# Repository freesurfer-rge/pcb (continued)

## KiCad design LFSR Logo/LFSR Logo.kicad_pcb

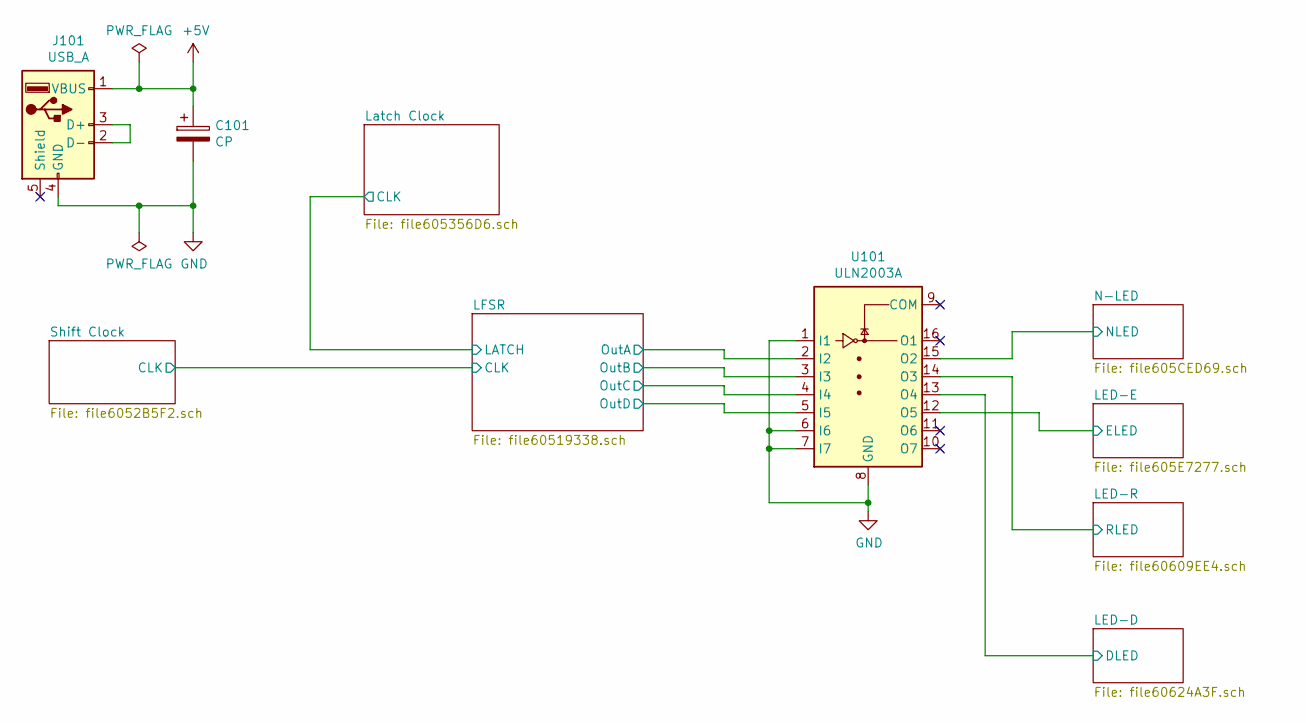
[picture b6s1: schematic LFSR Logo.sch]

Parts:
C101: CP; CP_Radial_D4.0mm_P1.50mm
J101: USB_A; USB_A_CONNFLY_DS1095-WNR0
U101: ULN2003A; DIP-16_W7.62mm

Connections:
+5V: C101.1, J101.1 (VBUS); also elsewhere on the board
/LED-D/DLED: U101.13 (O4); also elsewhere on the board
/LED-E/ELED: U101.12 (O5); also elsewhere on the board
/LED-R/RLED: U101.14 (O3); also elsewhere on the board
/LFSR/OutA: U101.2 (I2); also elsewhere on the board
/LFSR/OutB: U101.3 (I3); also elsewhere on the board
/LFSR/OutC: U101.4 (I4); also elsewhere on the board
/LFSR/OutD: U101.5 (I5); also elsewhere on the board
/N-LED/NLED: U101.15 (O2); also elsewhere on the board
GND: C101.2, J101.4 (GND), U101.1 (I1), U101.6 (I6), U101.7 (I7), U101.8 (GND); also elsewhere on the board
unnamed: J101.2 (D-), J101.3 (D+)

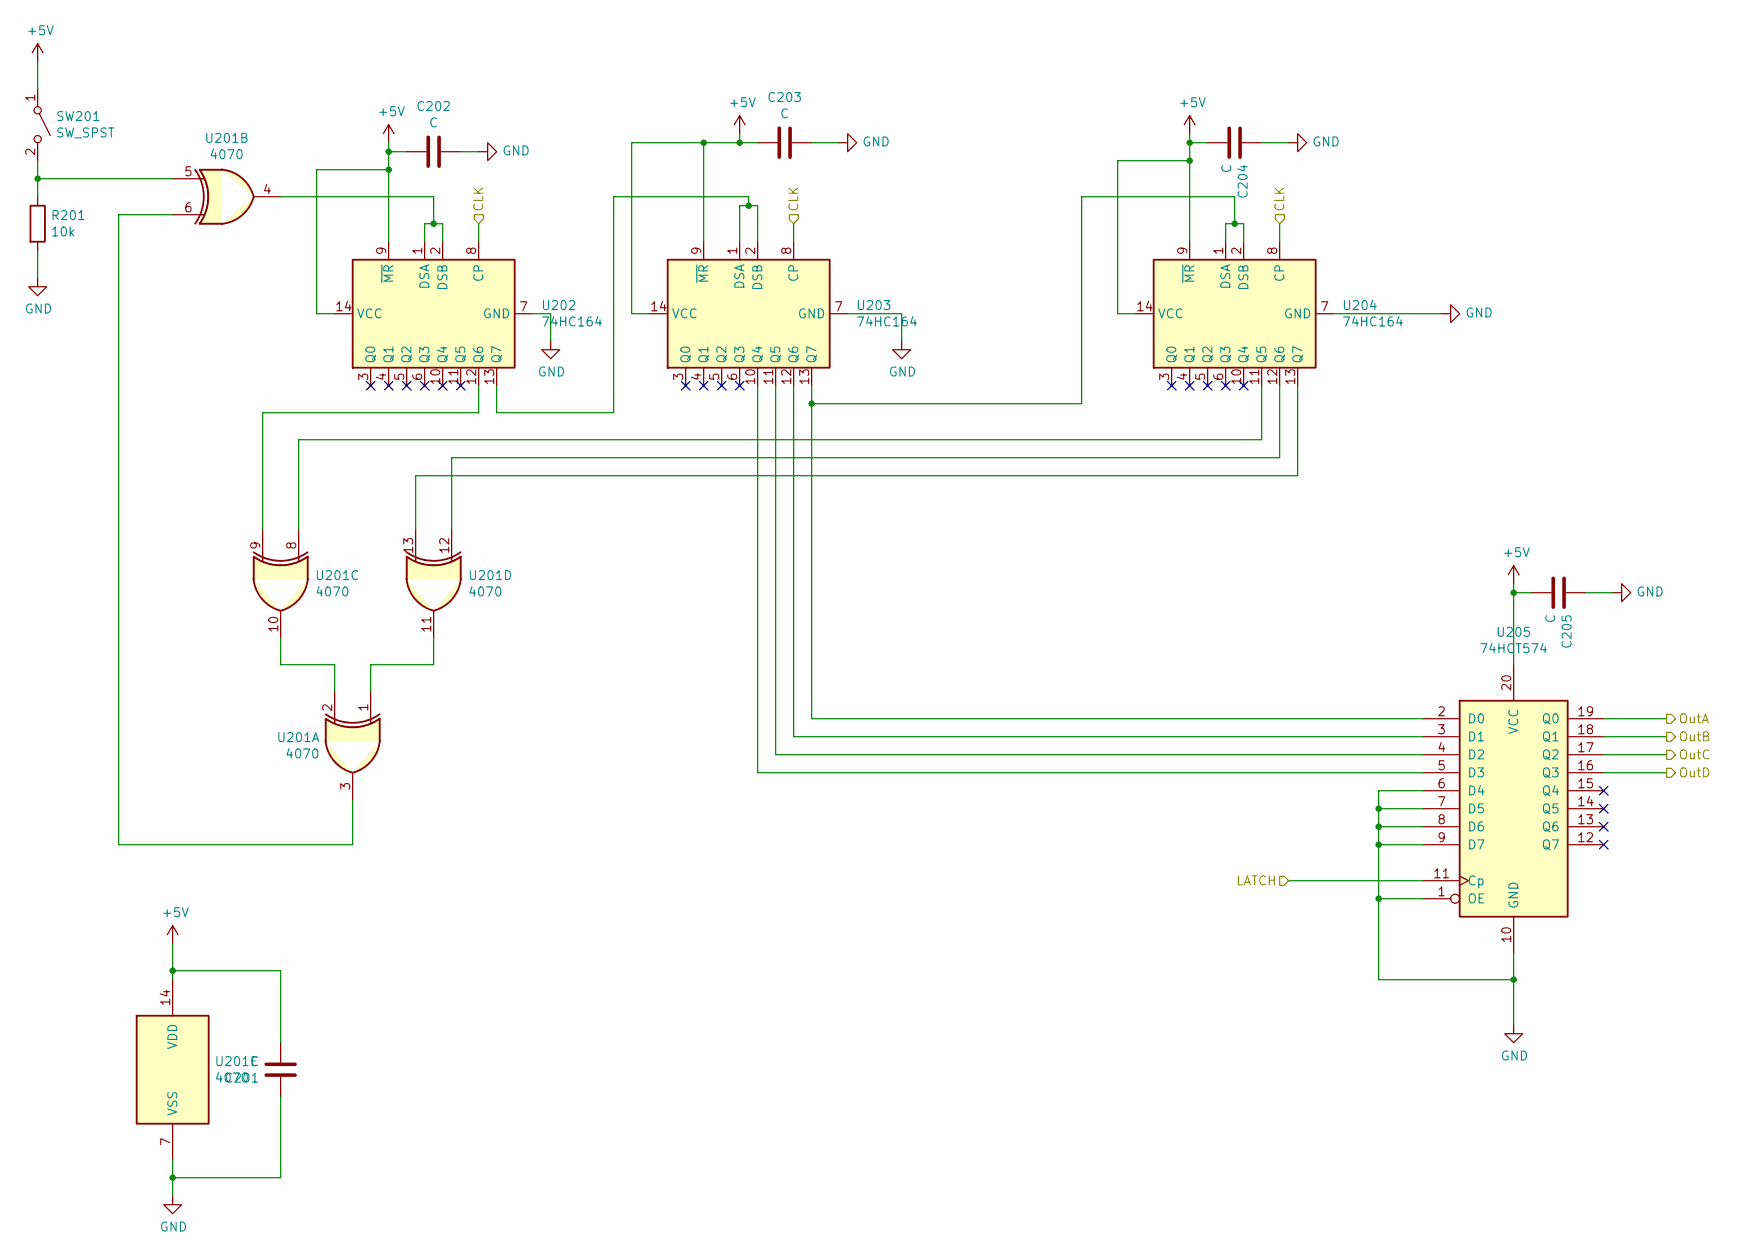
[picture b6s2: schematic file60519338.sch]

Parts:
C201, C202, C203, C204, C205: C; C_Disc_D4.3mm_W1.9mm_P5.00mm
R201: 10k; R_Axial_DIN0207_L6.3mm_D2.5mm_P7.62mm_Horizontal
SW201: SW_SPST; SW_PUSH_6mm
U201: 4070
U202, U203, U204: 74HC164; DIP-14_W7.62mm
U205: 74HCT574; DIP-20_W7.62mm

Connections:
+5V: C201.2, C202.2, C203.2, C204.2, C205.2, SW201.1 (A), U201.14 (VDD), U202.9 (~MR), U202.14 (VCC), U203.9 (~MR), U203.14 (VCC), U204.9 (~MR), U204.14 (VCC), U205.20 (VCC); also elsewhere on the board
/LFSR/CLK: U202.8 (CP), U203.8 (CP), U204.8 (CP); also elsewhere on the board
/LFSR/OutA: U205.19 (Q0); also elsewhere on the board
/LFSR/OutB: U205.18 (Q1); also elsewhere on the board
/LFSR/OutC: U205.17 (Q2); also elsewhere on the board
/LFSR/OutD: U205.16 (Q3); also elsewhere on the board
/Latch Clock/CLK: U205.11 (Cp); also elsewhere on the board
GND: C201.1, C202.1, C203.1, C204.1, C205.1, R201.2, U201.7 (VSS), U202.7 (GND), U203.7 (GND), U204.7 (GND), U205.1 (OE), U205.6 (D4), U205.7 (D5), U205.8 (D6), U205.9 (D7), U205.10 (GND); also elsewhere on the board
unnamed: R201.1, SW201.2 (B), U201.5
unnamed: U201.1, U201.11
unnamed: U201.3, U201.6
unnamed: U201.4, U202.1 (DSA), U202.2 (DSB)
unnamed: U201.8, U204.11 (Q5)
unnamed: U201.9, U202.12 (Q6)
unnamed: U201.2, U201.10
unnamed: U201.12, U204.12 (Q6)
unnamed: U201.13, U204.13 (Q7)
unnamed: U202.13 (Q7), U203.1 (DSA), U203.2 (DSB)
unnamed: U203.10 (Q4), U205.5 (D3)
unnamed: U203.11 (Q5), U205.4 (D2)
unnamed: U203.12 (Q6), U205.3 (D1)
unnamed: U203.13 (Q7), U204.1 (DSA), U204.2 (DSB), U205.2 (D0)

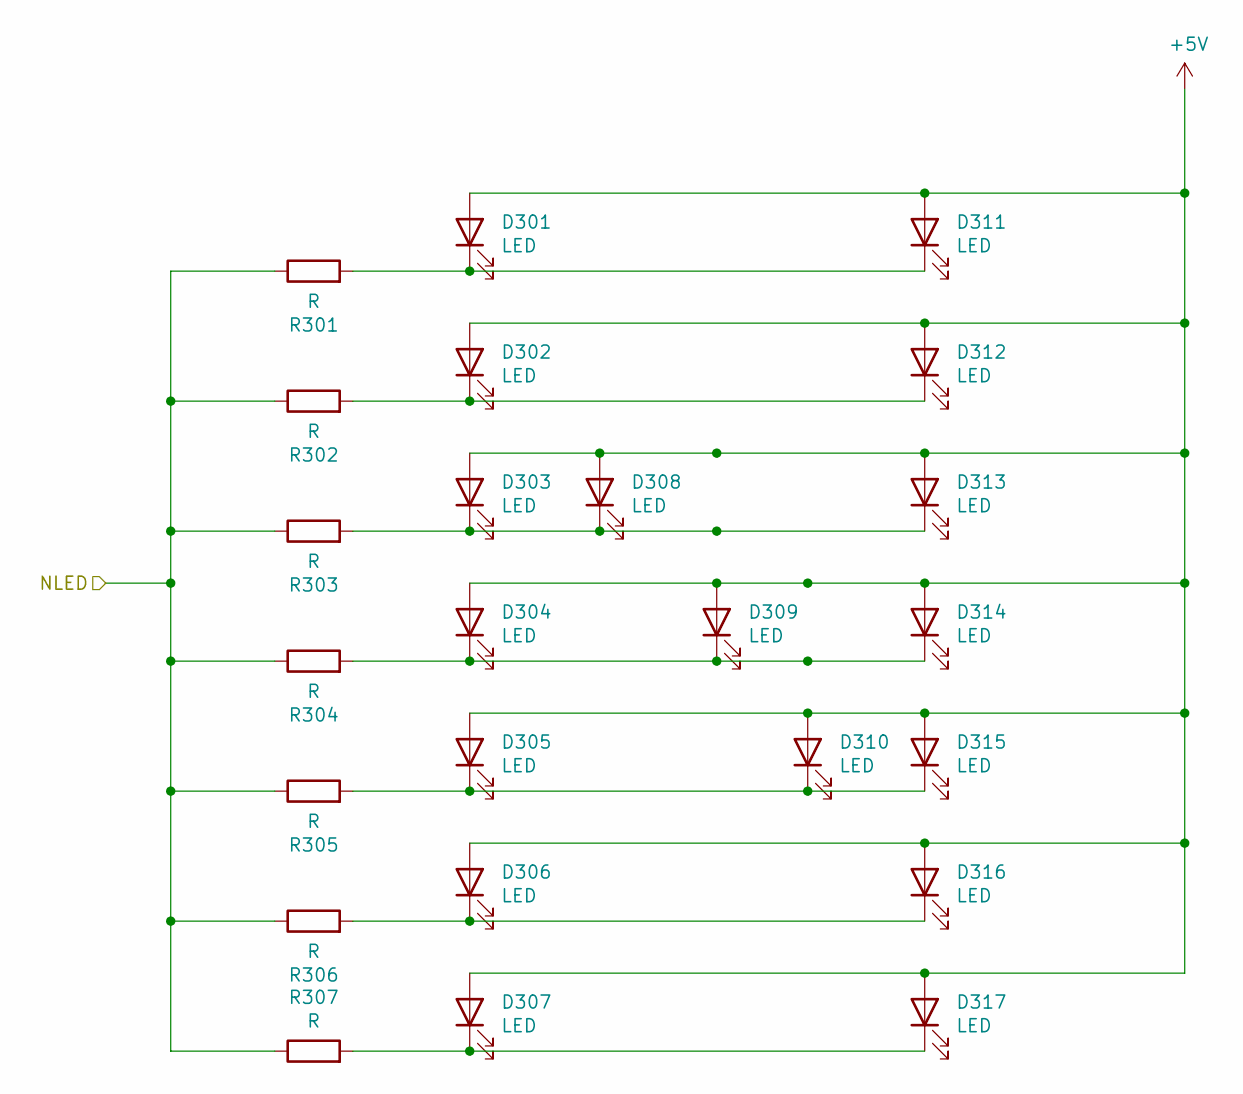
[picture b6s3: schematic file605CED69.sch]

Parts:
D301, D302, D303, D304, D305, D306, D307, D308, D309, D310, D311, D312, D313, D314, D315, D316, D317: LED; LED_D5.0mm
R301, R302, R303, R304, R305, R306, R307: R; R_Axial_DIN0207_L6.3mm_D2.5mm_P7.62mm_Horizontal

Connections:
+5V: D301.2 (A), D302.2 (A), D303.2 (A), D304.2 (A), D305.2 (A), D306.2 (A), D307.2 (A), D308.2 (A), D309.2 (A), D310.2 (A), D311.2 (A), D312.2 (A), D313.2 (A), D314.2 (A), D315.2 (A), D316.2 (A), D317.2 (A); also elsewhere on the board
/N-LED/NLED: R301.1, R302.1, R303.1, R304.1, R305.1, R306.1, R307.1; also elsewhere on the board
unnamed: D301.1 (K), D311.1 (K), R301.2
unnamed: D302.1 (K), D312.1 (K), R302.2
unnamed: D303.1 (K), D308.1 (K), D313.1 (K), R303.2
unnamed: D304.1 (K), D309.1 (K), D314.1 (K), R304.2
unnamed: D305.1 (K), D310.1 (K), D315.1 (K), R305.2
unnamed: D306.1 (K), D316.1 (K), R306.2
unnamed: D307.1 (K), D317.1 (K), R307.2

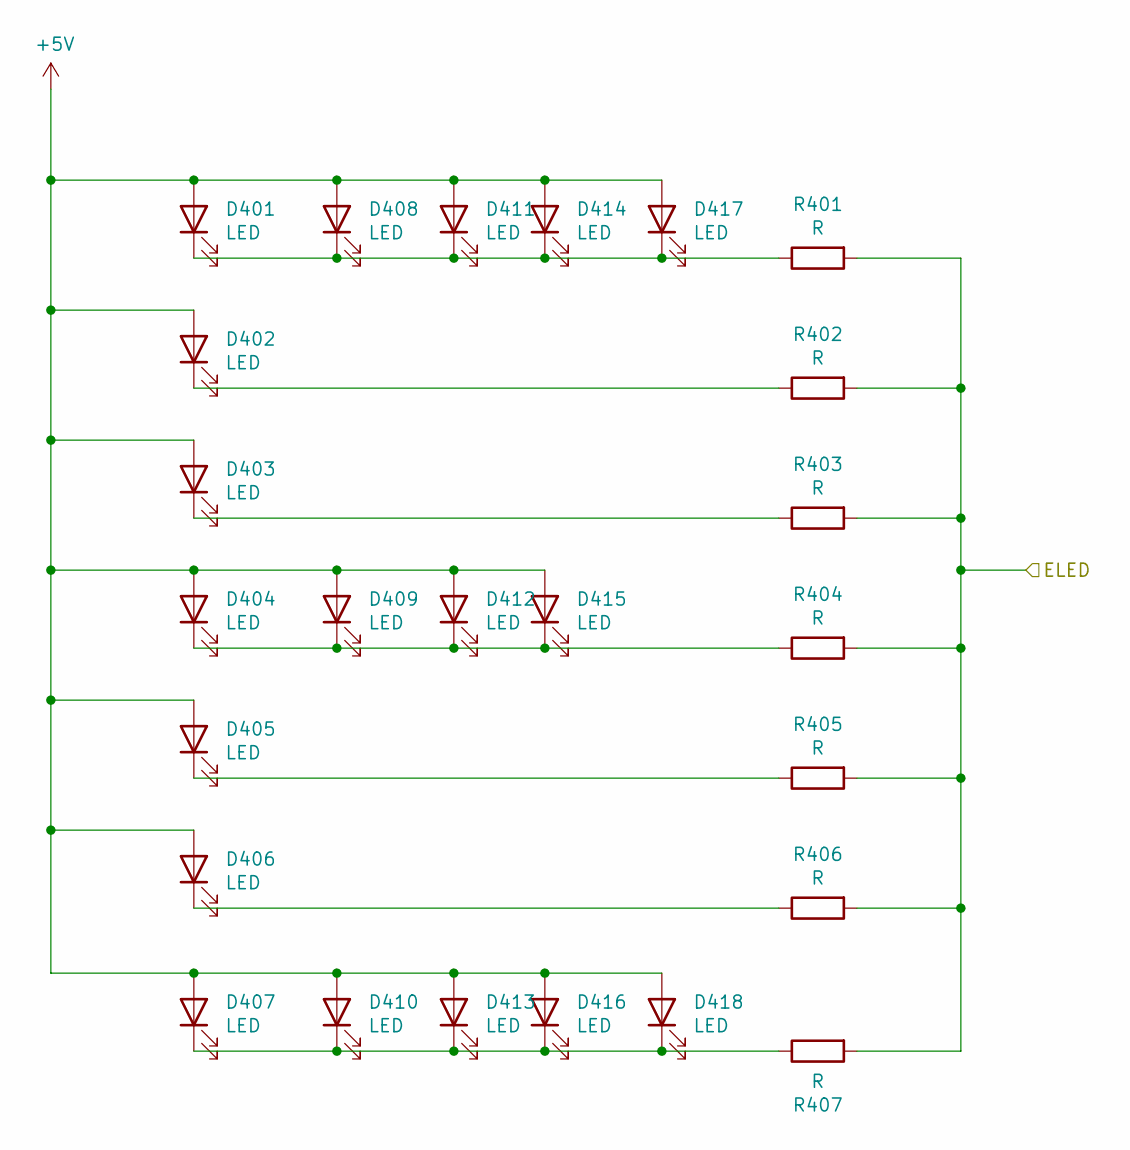
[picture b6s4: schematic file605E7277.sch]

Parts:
D401, D402, D403, D404, D405, D406, D407, D408, D409, D410, D411, D412, D413, D414, D415, D416, D417, D418: LED; LED_D5.0mm
R401, R402, R403, R404, R405, R406, R407: R; R_Axial_DIN0207_L6.3mm_D2.5mm_P7.62mm_Horizontal

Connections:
+5V: D401.2 (A), D402.2 (A), D403.2 (A), D404.2 (A), D405.2 (A), D406.2 (A), D407.2 (A), D408.2 (A), D409.2 (A), D410.2 (A), D411.2 (A), D412.2 (A), D413.2 (A), D414.2 (A), D415.2 (A), D416.2 (A), D417.2 (A), D418.2 (A); also elsewhere on the board
/LED-E/ELED: R401.2, R402.2, R403.2, R404.2, R405.2, R406.2, R407.2; also elsewhere on the board
unnamed: D401.1 (K), D408.1 (K), D411.1 (K), D414.1 (K), D417.1 (K), R401.1
unnamed: D402.1 (K), R402.1
unnamed: D403.1 (K), R403.1
unnamed: D404.1 (K), D409.1 (K), D412.1 (K), D415.1 (K), R404.1
unnamed: D405.1 (K), R405.1
unnamed: D406.1 (K), R406.1
unnamed: D407.1 (K), D410.1 (K), D413.1 (K), D416.1 (K), D418.1 (K), R407.1

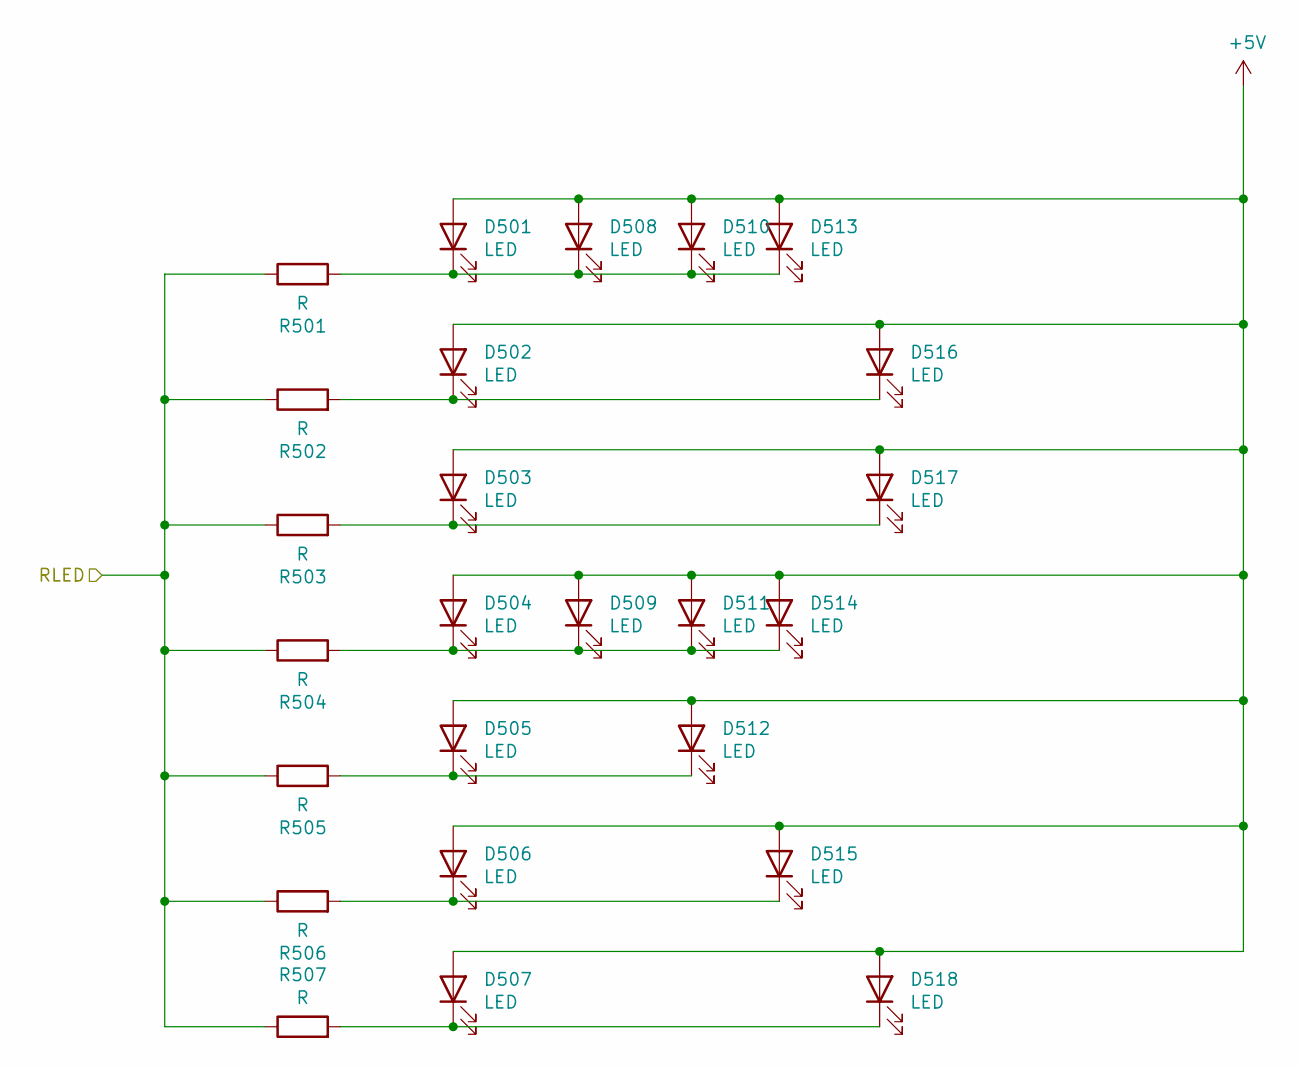
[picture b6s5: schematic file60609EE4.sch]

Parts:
D501, D502, D503, D504, D505, D506, D507, D508, D509, D510, D511, D512, D513, D514, D515, D516, D517, D518: LED; LED_D5.0mm
R501, R502, R503, R504, R505, R506, R507: R; R_Axial_DIN0207_L6.3mm_D2.5mm_P7.62mm_Horizontal

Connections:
+5V: D501.2 (A), D502.2 (A), D503.2 (A), D504.2 (A), D505.2 (A), D506.2 (A), D507.2 (A), D508.2 (A), D509.2 (A), D510.2 (A), D511.2 (A), D512.2 (A), D513.2 (A), D514.2 (A), D515.2 (A), D516.2 (A), D517.2 (A), D518.2 (A); also elsewhere on the board
/LED-R/RLED: R501.1, R502.1, R503.1, R504.1, R505.1, R506.1, R507.1; also elsewhere on the board
unnamed: D501.1 (K), D508.1 (K), D510.1 (K), D513.1 (K), R501.2
unnamed: D502.1 (K), D516.1 (K), R502.2
unnamed: D503.1 (K), D517.1 (K), R503.2
unnamed: D504.1 (K), D509.1 (K), D511.1 (K), D514.1 (K), R504.2
unnamed: D505.1 (K), D512.1 (K), R505.2
unnamed: D506.1 (K), D515.1 (K), R506.2
unnamed: D507.1 (K), D518.1 (K), R507.2

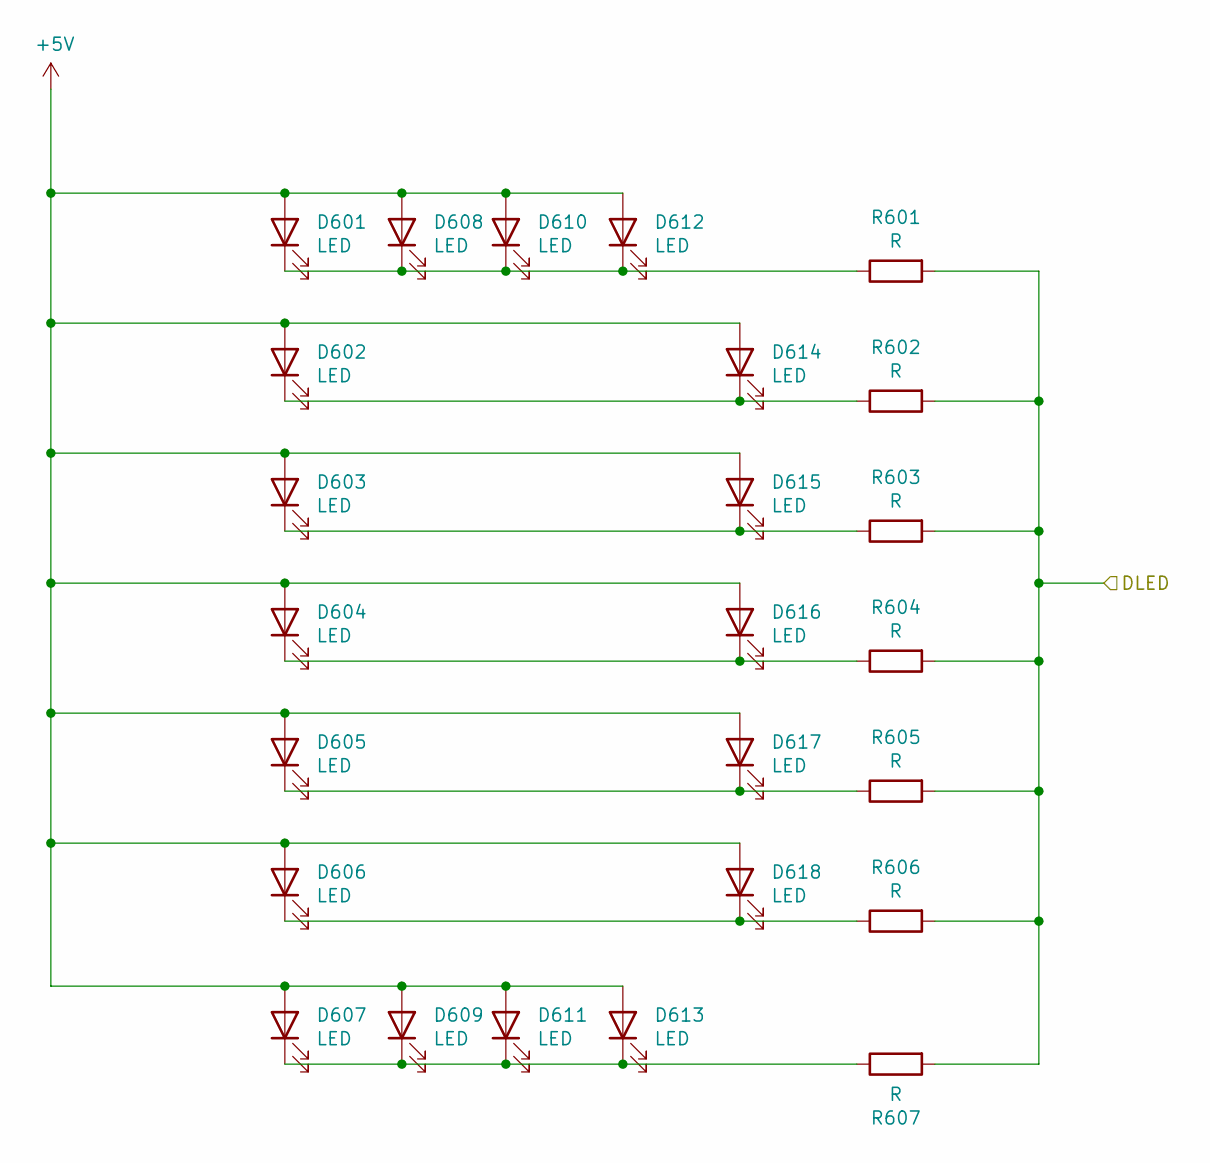
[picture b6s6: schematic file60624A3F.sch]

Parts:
D601, D602, D603, D604, D605, D606, D607, D608, D609, D610, D611, D612, D613, D614, D615, D616, D617, D618: LED; LED_D5.0mm
R601, R602, R603, R604, R605, R606, R607: R; R_Axial_DIN0207_L6.3mm_D2.5mm_P7.62mm_Horizontal

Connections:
+5V: D601.2 (A), D602.2 (A), D603.2 (A), D604.2 (A), D605.2 (A), D606.2 (A), D607.2 (A), D608.2 (A), D609.2 (A), D610.2 (A), D611.2 (A), D612.2 (A), D613.2 (A), D614.2 (A), D615.2 (A), D616.2 (A), D617.2 (A), D618.2 (A); also elsewhere on the board
/LED-D/DLED: R601.2, R602.2, R603.2, R604.2, R605.2, R606.2, R607.2; also elsewhere on the board
unnamed: D601.1 (K), D608.1 (K), D610.1 (K), D612.1 (K), R601.1
unnamed: D602.1 (K), D614.1 (K), R602.1
unnamed: D603.1 (K), D615.1 (K), R603.1
unnamed: D604.1 (K), D616.1 (K), R604.1
unnamed: D605.1 (K), D617.1 (K), R605.1
unnamed: D606.1 (K), D618.1 (K), R606.1
unnamed: D607.1 (K), D609.1 (K), D611.1 (K), D613.1 (K), R607.1

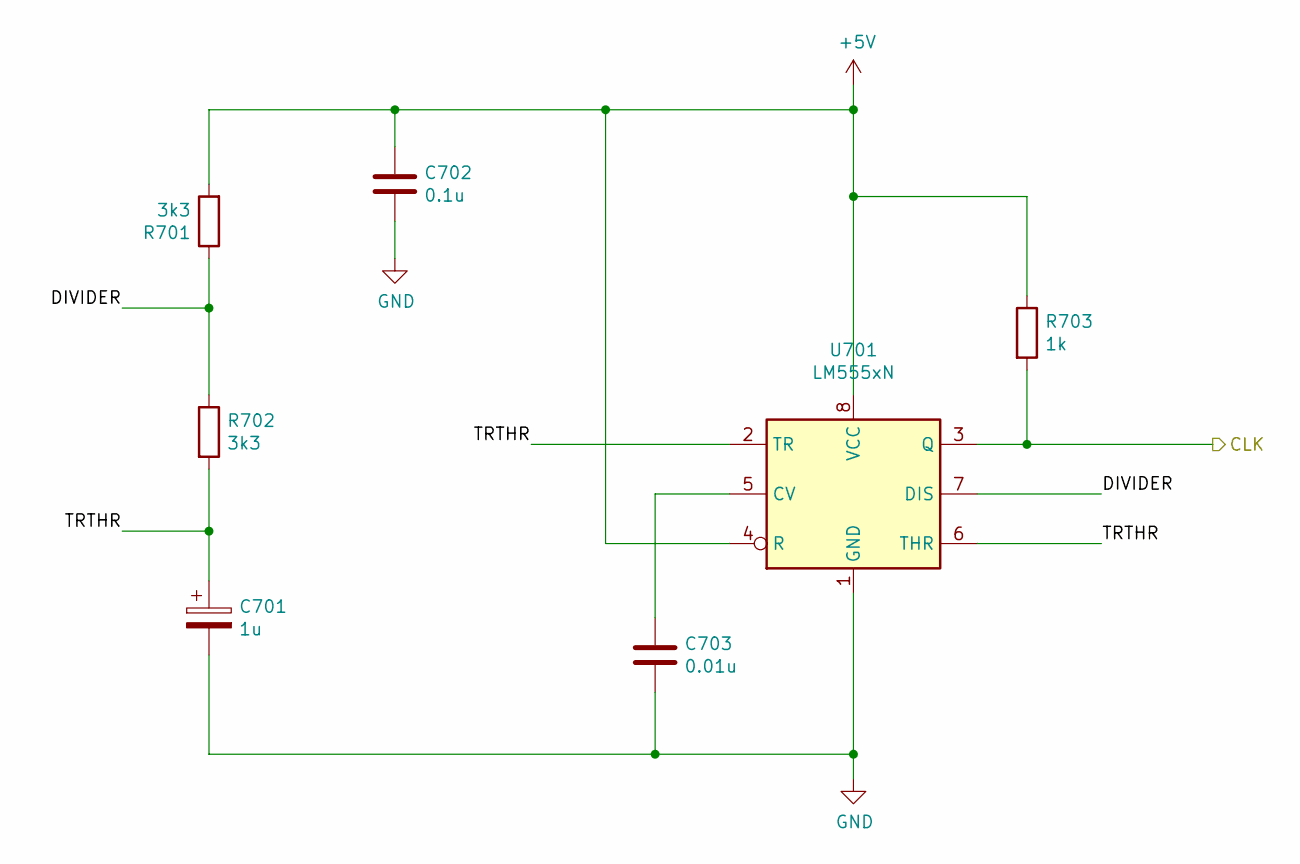
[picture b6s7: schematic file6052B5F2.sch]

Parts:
C701: 1u; CP_Radial_D4.0mm_P1.50mm
C702: 0.1u; C_Disc_D4.3mm_W1.9mm_P5.00mm
C703: 0.01u; C_Disc_D3.4mm_W2.1mm_P2.50mm
R701, R702: 3k3; R_Axial_DIN0207_L6.3mm_D2.5mm_P7.62mm_Horizontal
R703: 1k; R_Axial_DIN0207_L6.3mm_D2.5mm_P7.62mm_Horizontal
U701: LM555xN; DIP-8_W7.62mm

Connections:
+5V: C702.2, R701.2, R703.1, U701.4 (R), U701.8 (VCC); also elsewhere on the board
/LFSR/CLK: R703.2, U701.3 (Q); also elsewhere on the board
/Shift Clock/DIVIDER: R701.1, R702.1, U701.7 (DIS)
/Shift Clock/TRTHR: C701.1, R702.2, U701.2 (TR), U701.6 (THR)
GND: C701.2, C702.1, C703.2, U701.1 (GND); also elsewhere on the board
unnamed: C703.1, U701.5 (CV)

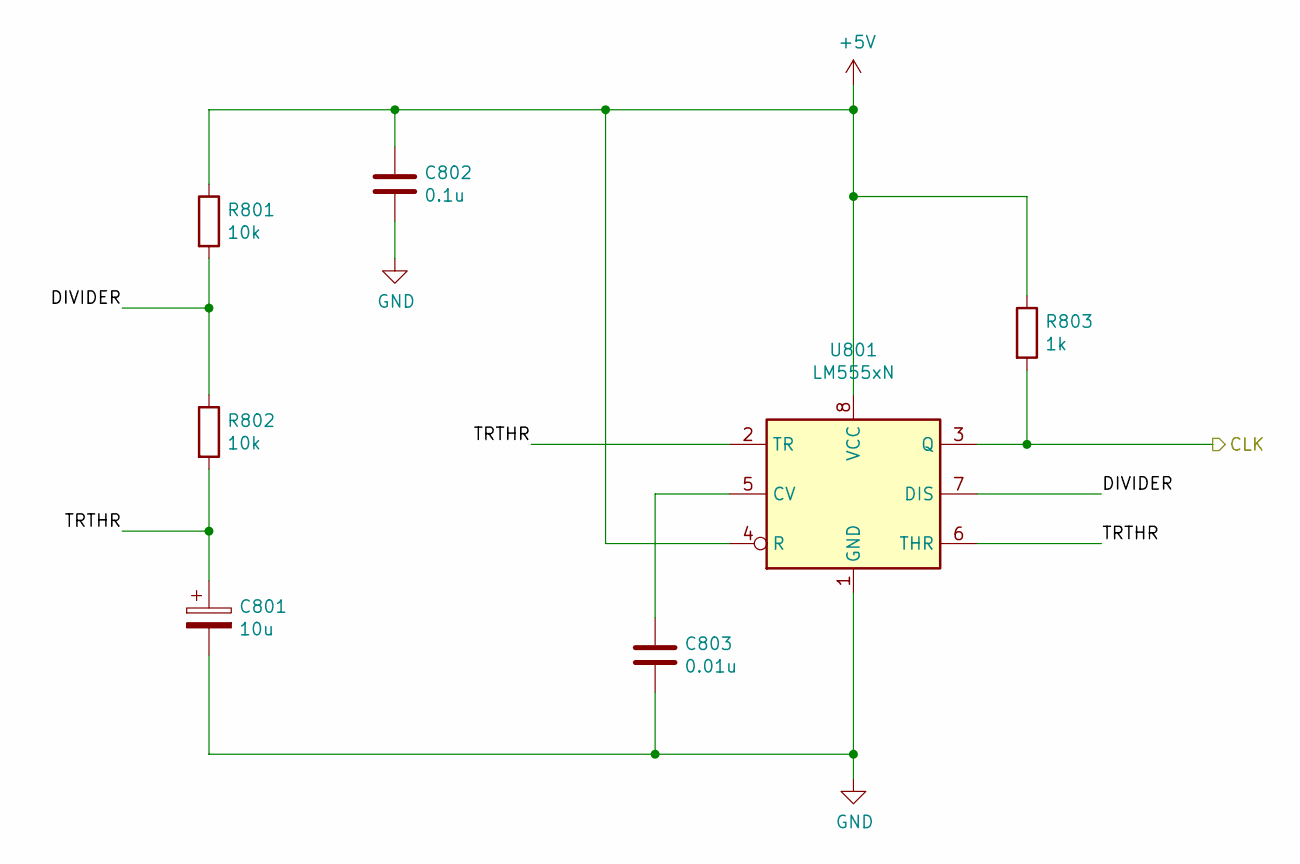
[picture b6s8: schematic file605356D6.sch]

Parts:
C801: 10u; CP_Radial_D4.0mm_P1.50mm
C802: 0.1u; C_Disc_D4.3mm_W1.9mm_P5.00mm
C803: 0.01u; C_Disc_D3.4mm_W2.1mm_P2.50mm
R801, R802: 10k; R_Axial_DIN0207_L6.3mm_D2.5mm_P7.62mm_Horizontal
R803: 1k; R_Axial_DIN0207_L6.3mm_D2.5mm_P7.62mm_Horizontal
U801: LM555xN; DIP-8_W7.62mm

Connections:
+5V: C802.2, R801.1, R803.1, U801.4 (R), U801.8 (VCC); also elsewhere on the board
/Latch Clock/CLK: R803.2, U801.3 (Q); also elsewhere on the board
/Latch Clock/DIVIDER: R801.2, R802.1, U801.7 (DIS)
/Latch Clock/TRTHR: C801.1, R802.2, U801.2 (TR), U801.6 (THR)
GND: C801.2, C802.1, C803.2, U801.1 (GND); also elsewhere on the board
unnamed: C803.1, U801.5 (CV)

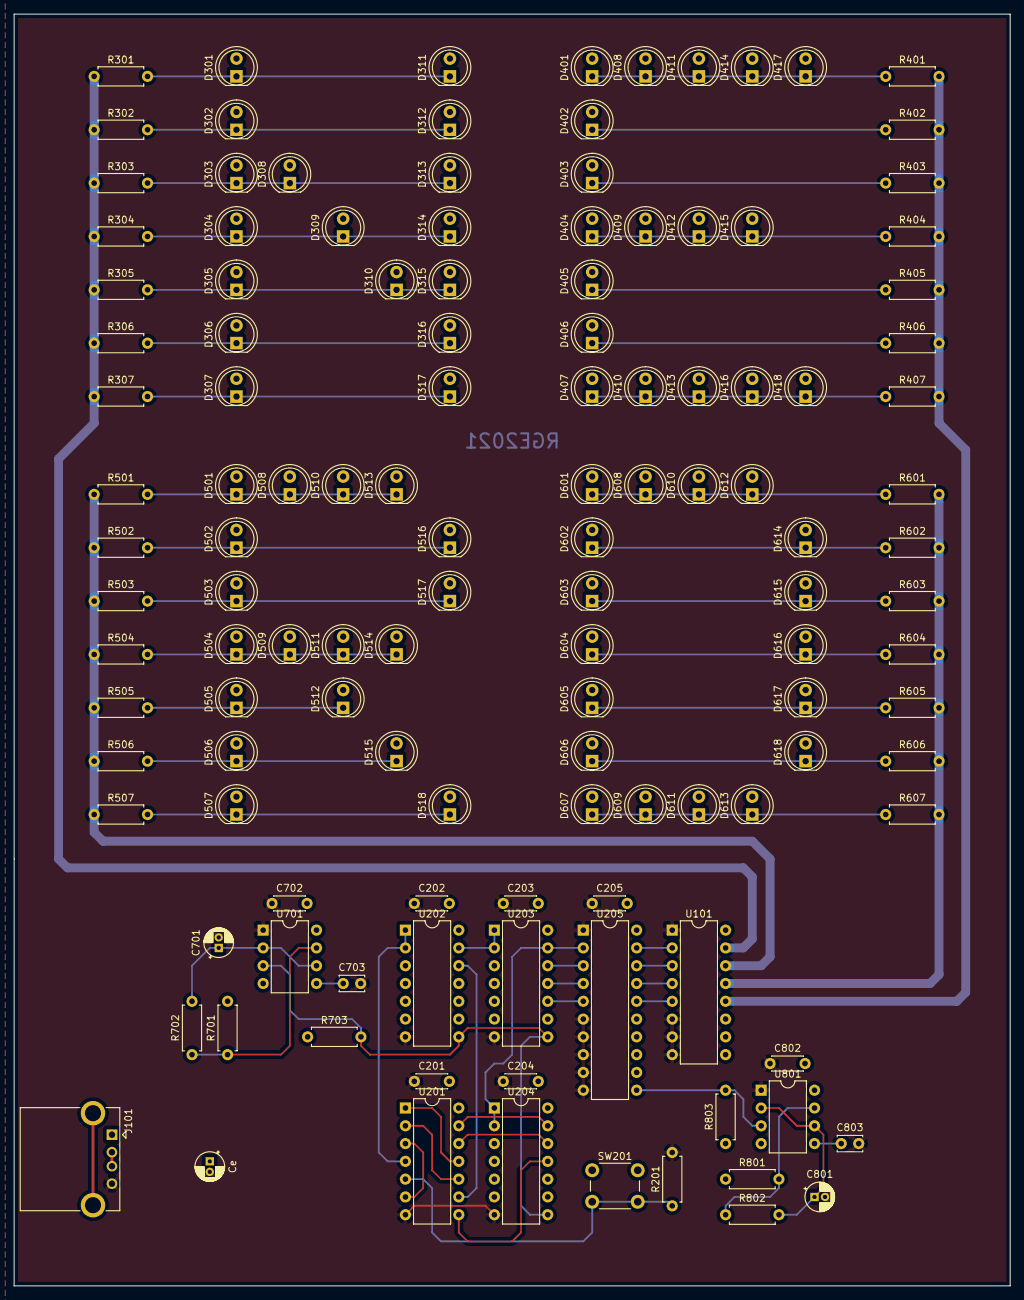
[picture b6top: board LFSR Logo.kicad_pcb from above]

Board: 2 copper layers, 142.2 x 181.6 mm, 128 parts (0 on the bottom side), 61 nets.

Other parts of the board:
Ce: CP; CP_Radial_D4.0mm_P1.50mm

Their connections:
+5V: Ce.1; also elsewhere on the board
GND: Ce.2; also elsewhere on the board

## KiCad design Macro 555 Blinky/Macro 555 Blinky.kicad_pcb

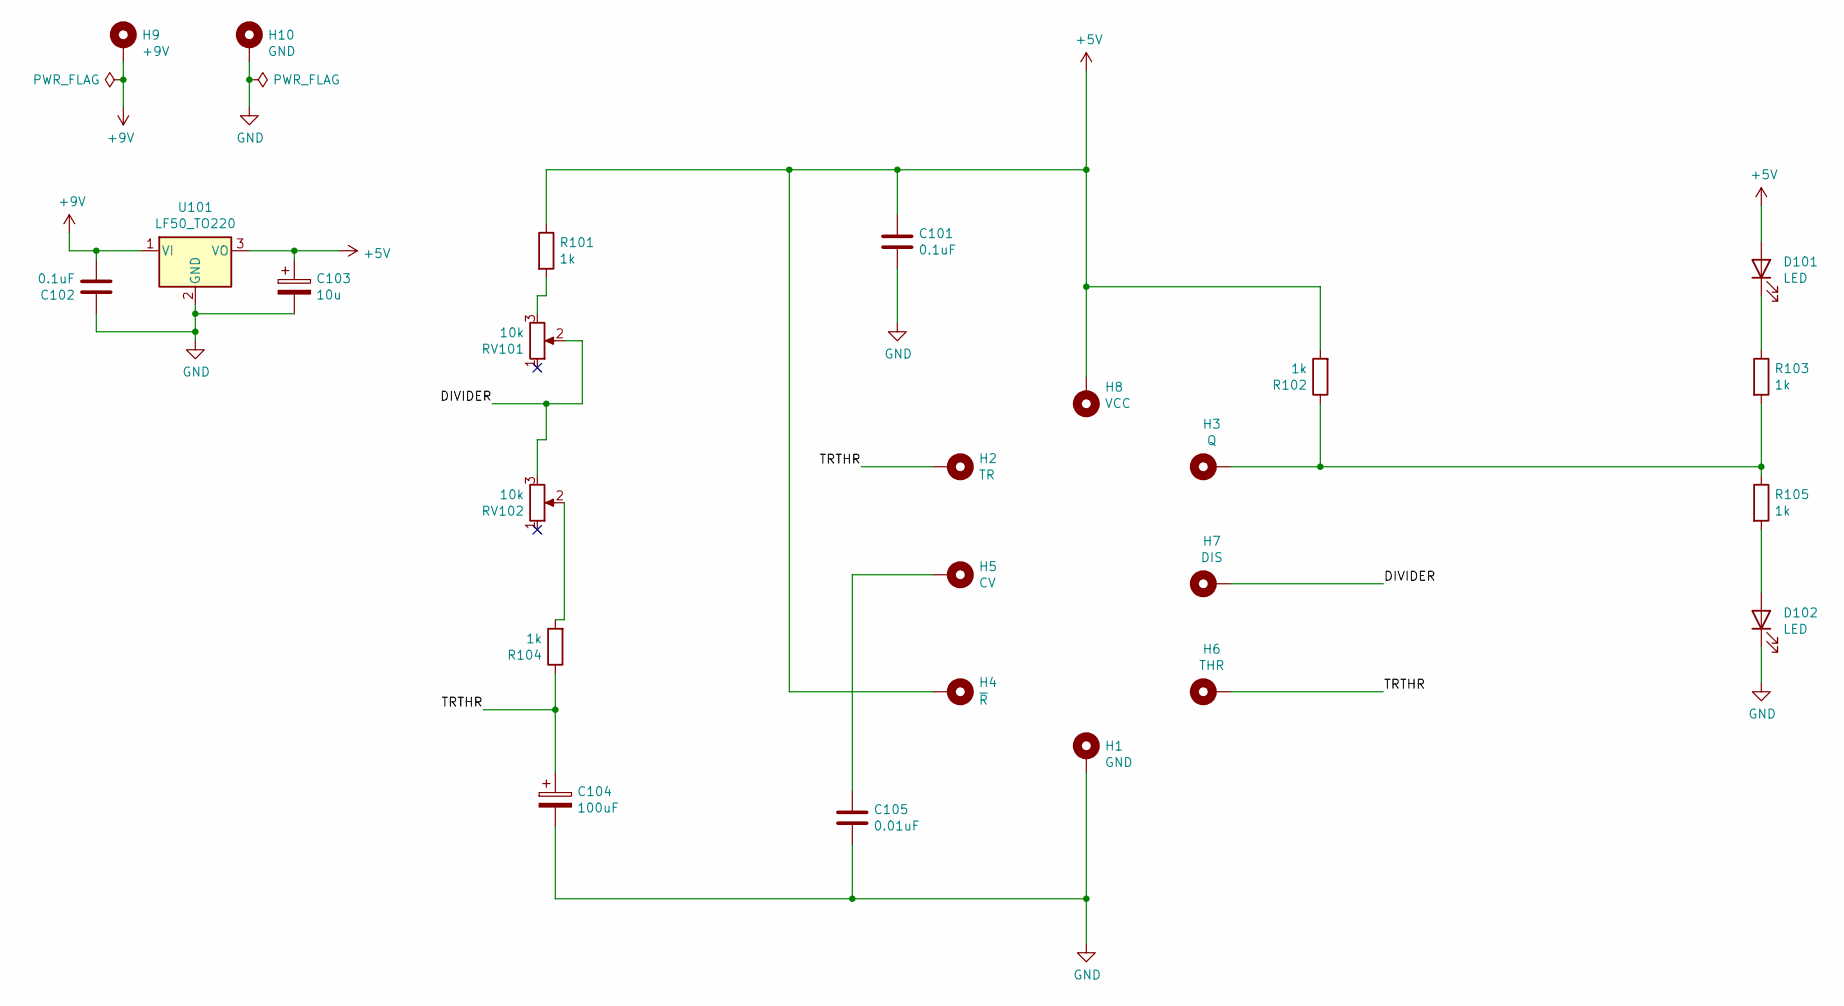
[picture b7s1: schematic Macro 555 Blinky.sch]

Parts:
C101, C102: 0.1uF; C_Disc_D4.3mm_W1.9mm_P5.00mm
C103: 10u; CP_Radial_D4.0mm_P1.50mm
C104: 100uF; CP_Radial_D4.0mm_P1.50mm
C105: 0.01uF; C_Disc_D3.0mm_W2.0mm_P2.50mm
D101, D102: LED; LED_D5.0mm
H1, H10: GND; Pin_D1.0mm_L10.0mm
H2: TR; Pin_D1.0mm_L10.0mm
H3: Q; Pin_D1.0mm_L10.0mm
H4: ~R; Pin_D1.0mm_L10.0mm
H5: CV; Pin_D1.0mm_L10.0mm
H6: THR; Pin_D1.0mm_L10.0mm
H7: DIS; Pin_D1.0mm_L10.0mm
H8: VCC; Pin_D1.0mm_L10.0mm
H9: +9V; Pin_D1.0mm_L10.0mm
R101, R102, R103, R104, R105: 1k; R_Axial_DIN0207_L6.3mm_D2.5mm_P7.62mm_Horizontal
RV101, RV102: 10k; Potentiometer_ACP_CA9-V10_Vertical
U101: LF50_TO220; TO-220-3_Horizontal_TabDown

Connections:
+5V: C101.1, C103.1, D101.2 (A), H4.1, H8.1, R101.1, R102.2, U101.3 (VO)
+9V: C102.2, H9.1, U101.1 (VI)
/DIVIDER: H7.1, RV101.2, RV102.3
/TRTHR: C104.1, H2.1, H6.1, R104.1
GND: C101.2, C102.1, C103.2, C104.2, C105.1, D102.1 (K), H1.1, H10.1, U101.2 (GND)
unnamed: C105.2, H5.1
unnamed: D101.1 (K), R103.1
unnamed: D102.2 (A), R105.2
unnamed: H3.1, R102.1, R103.2, R105.1
unnamed: R101.2, RV101.3
unnamed: R104.2, RV102.2

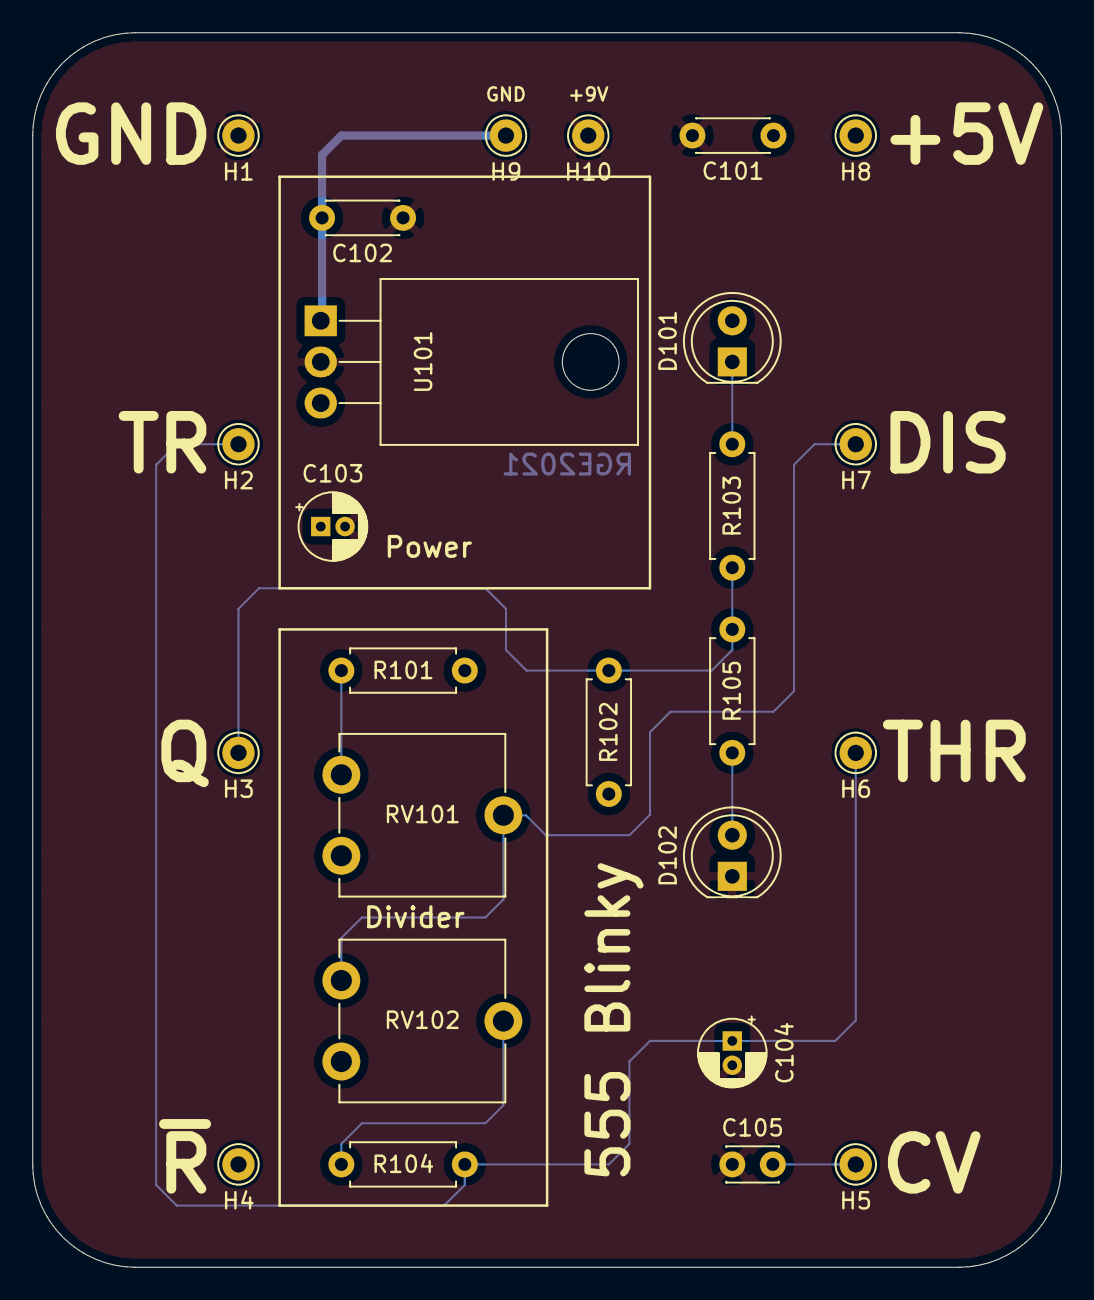
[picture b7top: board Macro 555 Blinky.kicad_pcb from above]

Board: 2 copper layers, 63.5 x 76.2 mm, 25 parts (0 on the bottom side), 11 nets.
